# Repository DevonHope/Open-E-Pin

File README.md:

# Open E-Pin

An open-source, battery-powered e-ink pin you can wear on a jacket or bag. It has a round
1.69" colour e-paper display, Bluetooth Low Energy and a small rechargeable battery. You pick
a photo in the Android app, place it in the circle, and the app converts it to the panel's six
colours and sends it to the pin. E-paper keeps the picture with no power at all, so the pin
sleeps until you press its button.

> **Status: v0.2, work in progress.** The board is designed and fully routed, the case is
> modelled and fit-checked against every part, and the firmware and app frameworks build and
> pass their unit tests. v0.2 fixes the findings of a full design audit
> ([hardware/docs/audit](hardware/docs/audit/STATUS.md)). Nothing has been built or run on real
> hardware yet: check the open items in that status table before ordering boards.

## Features

- **Round colour e-paper:** Good Display GDEH0169E02, 1.69", 400 x 400 pixels, six colours
  (Spectra 6). The image stays on screen with the power off.
- **Bluetooth Low Energy:** Nordic nRF52840 in a pre-certified Raytac MDBT50Q-1MV2 module.
- **Tiny sleep current:** the pin sleeps in System OFF (about 0.6 uA estimated, including the
  battery monitor) and only wakes on a button press. The display supply is switched off between refreshes.
- **Small rechargeable battery:** 3.7 V 60 mAh LiPo on a JST-PH connector, so it can be
  unplugged or swapped.
- **Safe charging over USB-C:** TI BQ25101 charger at 30 mA, with a thermistor against the cell
  so it only charges between 0 °C and 60 °C.
- **Protected inputs:** reverse-battery protection, plus a resettable fuse, ESD array and
  overvoltage cutoff on USB.
- **Resumable uploads:** if the Bluetooth link drops mid-transfer, the app picks up where it
  stopped. Each image is checked with a CRC before it's drawn.
- **Printed case** with a clean front, screws from the back and two locking pin-back posts.
- **Fully open:** KiCad schematic and board, case model, firmware and app, plus the scripts
  that generate the hardware files.

## Specifications

| | |
|---|---|
| Display | Good Display GDEH0169E02, 1.69" round, 400 x 400, Spectra 6, 32-pin 0.5 mm FPC |
| MCU / radio | Raytac MDBT50Q-1MV2 (nRF52840, Bluetooth 5, chip antenna) |
| Battery | 3.7 V LiPo, 60 mAh, JST-PH 2.0 mm, cell has its own protection circuit |
| Charging | USB-C, 30 mA, temperature-qualified (BQ25101) |
| Power | 3.0 V LDO (TPS7A0230), switched display rail (TPS22916C) |
| Controls | One side-press button, charge LED |
| Board | 56 mm round with a flat for the display ribbon, 4 layers, all parts on the back |
| Case | 3D-printed bezel and back cover, 60.4 mm across, 10.9 mm thick |
| Firmware | Zephyr / nRF Connect SDK, flashed over SWD test pads |
| App | Android 8.0 (API 26) or newer, Kotlin and Jetpack Compose |

## How it works

```mermaid
flowchart LR
    APP["Android app<br/>crop, dither, pack"] -. "Bluetooth LE" .-> MCU
    USB["USB-C"] --> CHG["Fuse, ESD,<br/>30 mA charger"] --> SYS(("Battery rail"))
    BAT["60 mAh LiPo"] --> RP["Reverse-battery<br/>protection"] --> SYS
    SYS --> LDO["3.0 V LDO"] --> MCU["nRF52840 module"]
    LDO --> SW["Display load switch"] --> EPD["1.69in round e-paper"]
    MCU -- "SPI" --> EPD
    BTN["Side button"] --> MCU
```

1. Press the button. The pin wakes and advertises as `Open E-Pin` for 60 seconds.
2. In the app, pick a photo, drag and pinch it into the circle, and adjust it. The app dithers
   it to the six ink colours and packs it two pixels per byte.
3. The app connects and uploads the image. The pin checks it, switches the display on, draws
   it, switches the display off again and goes back to sleep.

The Bluetooth protocol shared by the app and firmware is in
[`docs/ble-protocol.md`](docs/ble-protocol.md).

## Hardware

The board is a 56 mm round, 4-layer PCB with every part on the back and the display on the
front. The schematic and board are generated from one Python file,
[`hardware/scripts/design.py`](hardware/scripts/design.py), which lists every part and
connection, and the board is autorouted by a script. See the
[hardware README](hardware/README.md) for the block diagram, pin map, safety notes,
regeneration and routing steps, and the open items to check before ordering boards. The parts
list is in [`hardware/bom/open-e-pin-bom.csv`](hardware/bom/open-e-pin-bom.csv), and there is
a [PDF of the schematic](hardware/docs/schematic.pdf) if you don't have KiCad.

## Case

| Exploded view | Back |
|---|---|
|  |  |

A two-part printed case: a **bezel** with the display window, and a **back cover**. Two M2
countersunk thread-forming screws go in from the back into bosses in the bezel, so the front
is just the ring and the display, and two snap hooks hold the top. Two locking tie tack posts
stop the pin from spinning on a bag. They are fitted from inside the back cover, so their heads
can't pull through, and a printed retainer bar holds them in place. A small printed plunger
works the side button.

The [SolidCraft](hardware/case/solidcraft/) design is the master for the case; the printable
STEP and STL files in [`hardware/case/out/`](hardware/case/out/) are exported from it. The
[case README](hardware/case/README.md) has the fastener list, fit-check measurements,
assembly steps and the assumptions to check on real parts.

## Firmware

Zephyr-based firmware for the nRF52840 in [`firmware/`](firmware/). It sleeps in System OFF,
wakes on the button, advertises, receives an image over a custom GATT service, checks its
CRC-32 and draws it on the panel. It also reports battery level through the standard Battery
Service. It builds for the pin board (`open_e_pin/nrf52840`) and for an nRF52840 DK for bench
work, and the transfer logic has unit tests that run on a PC.

The panel driver follows Good Display's sample code for this panel but hasn't been run on
a real panel yet. See the [firmware README](firmware/README.md) for building, flashing, logs over
RTT, and the checklist before powering a real panel.

## Android app

A Kotlin app in [`app/`](app/) that finds the pin, lets you pick an image with the system photo
picker and place it in the round frame, then adjusts, dithers and uploads it. All the image
and protocol logic lives in a plain-Kotlin `core` module with unit tests, and the `android`
module holds the Jetpack Compose UI and BLE code. The UI hasn't been run on a phone yet. See
the [app README](app/README.md) for the image pipeline, building and permissions.

## Repository layout

| Path | What it is |
|---|---|
| [`hardware/`](hardware/) | Main board: KiCad 7 project, generator and routing scripts, BOM, docs |
| [`hardware/case/`](hardware/case/) | Printed case: SolidCraft master, STEP/STL exports, fit check |
| [`firmware/`](firmware/) | nRF52840 firmware (Zephyr / nRF Connect SDK) |
| [`app/`](app/) | Android companion app (Kotlin, Jetpack Compose) |
| [`docs/ble-protocol.md`](docs/ble-protocol.md) | Bluetooth protocol between the app and the pin |
| [`GDEH0169E02.pdf`](GDEH0169E02.pdf) | Display specification from Good Display, kept for reference |

## Roadmap

- [x] Schematic and part selection
- [x] Board placement and routing
- [x] Printed case, fit-checked against the board, battery and display
- [x] Firmware framework: sleep and wake, BLE image transfer with resume, battery reporting
- [x] App framework: image pipeline, dithering, resumable uploader
- [ ] Check the [open items](hardware/README.md) on real parts (display ribbon fold, battery
      thickness, footprints) and order the first boards
- [ ] Port the real panel init sequence and test on a panel
- [ ] Run the app on a phone against the firmware
- [ ] Print and assemble a case
- [ ] Bonding so only a paired phone can send images, and over-the-air firmware updates

## Contributing

Issues and pull requests are welcome, especially reviews of the schematic and case before the
first boards are ordered. A few conventions keep things in sync:

- **Board:** edit `hardware/scripts/design.py` and regenerate rather than editing the KiCad
  files by hand.
- **Case:** edit the SolidCraft design and re-export to `hardware/case/out/`.
- **Protocol:** change [`docs/ble-protocol.md`](docs/ble-protocol.md) first, then the firmware
  and app together.

## License

GPL-3.0. See [LICENSE](LICENSE).

The display specification (`GDEH0169E02.pdf`) is © Good Display and is included only for
reference. It is not covered by this project's license.

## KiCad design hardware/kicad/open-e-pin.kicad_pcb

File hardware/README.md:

# Open E-Pin hardware

KiCad 7 project for the main board. The schematic and board are **generated** from
[`scripts/design.py`](scripts/design.py), which lists every part and every connection.
Change the design there, then regenerate, so the schematic and board never drift apart.

## Files

| Path | What it is |
|---|---|
| `kicad/open-e-pin.kicad_sch` | Schematic (one sheet, every pin labelled with its net) |
| `kicad/open-e-pin.kicad_pcb` | Board: 56 mm round with a flat for the display ribbon, 2 case-screw holes (4.6 mm, unplated, for the bezel's screw bosses), 2 notches for the case's snap hooks, 3 fiducials, 4 layers (0.8 mm), placed and routed |
| `kicad/open-e-pin.kicad_pro` | Project, including the net classes and board rules the board is routed to (written by `route.py prep`), so KiCad's DRC checks the real rules |
| `kicad/open-e-pin.kicad_sym` | Custom symbols (BQ25101, TPS7A0230, TPS22916C, GDEH0169E02 FPC) |
| `kicad/OpenEPin.pretty` | Custom footprints for TI's YFP packages (BQ25101, TPS22916C), written by `scripts/gen_footprints.py` |
| `case/` | Printed case, fit check and fastener list, see [case/README.md](case/README.md) |
| `bom/open-e-pin-bom.csv` | Bill of materials: manufacturer part numbers for every part, plus the battery, display, case parts, fasteners, pin hardware and consumables |
| `fab/` | Fabrication and assembly outputs (Gerber X2, drill, IPC-D-356 netlist, pick-and-place, fab notes), written by `scripts/gen_fab.sh` |
| `docs/audit/` | v0.1 design and manufacturing audit, and the status of each finding |
| `docs/schematic.pdf` | Schematic as a PDF |
| `docs/placement-back.png`, `docs/placement.csv` | Part placement view and coordinates |
| `docs/routing.png` | Back and front copper |
| `scripts/` | `design.py` (parts and nets), `gen_footprints.py`, `gen_schematic.py`, `gen_board.py`, `route.py`, `gen_bom.py`, `export_envelope.py` (part sizes for the case) |

## Regenerating

Needs KiCad 7 and its Python module (`pcbnew`). On Linux the system `python3` has it; on
Windows use the Python that ships with KiCad (`C:\Program Files\KiCad\7.0\bin\python.exe`)
and set `KICAD7_SYMBOL_DIR` and `KICAD7_FOOTPRINT_DIR` to KiCad's `share\kicad\symbols` and
`share\kicad\footprints` folders.

```
cd hardware/scripts
python3 design.py          # checks parts and nets
python3 gen_footprints.py  # writes kicad/OpenEPin.pretty
python3 gen_schematic.py   # writes kicad/open-e-pin.kicad_sch and the symbol library
python3 gen_board.py       # writes kicad/open-e-pin.kicad_pcb (overwrites placement!)
python3 gen_bom.py         # writes bom/open-e-pin-bom.csv
```

After routing (below), `./gen_fab.sh` writes the fabrication files to `fab/`.

### Routing

`gen_board.py` writes an unrouted board, so routing is redone after it. Needs Java 17 or later
and [Freerouting 1.9.0](https://github.com/freerouting/freerouting/releases/tag/v1.9.0)
(2.x ignores its pass limit when run from the command line and never saves).

```
python3 route.py prep      # rules, net classes, planes, GND/3V0 via fan-out; writes build/open-e-pin.dsn
java -jar freerouting-1.9.0.jar -de ../build/open-e-pin.dsn -do ../build/open-e-pin.ses -mp 100
python3 route.py import ../build/open-e-pin.ses
```

On a Linux machine with no screen, put `xvfb-run -a` in front of the `java` command.
`import` loads the autorouted tracks, fans out any GND/3V0 pad the autorouter boxed in
(ripping up the signal tracks round it if it has to),
rips up and re-routes any net that is still open or breaks clearance (a small maze router in
`route.py`), then adds GND pours on both outer layers and stitches them to the GND plane.

Stackup: B.Cu parts and signals, In1.Cu solid GND, In2.Cu 3V0 plane, F.Cu signals and GND
pour under the display. Rules (net classes in `kicad/open-e-pin.kicad_pro`): 0.15 mm tracks and
clearance, 0.2 mm for power (narrow enough to leave the 0.4 mm-pitch TI WCSP balls, and
`EPD_VDD` is in this class), 0.3 mm for the display booster, and 0.2 mm tracks with 0.2 mm
spacing for every panel rail (`PanelHV`: VGH, VGL, VSH1-3, VSL1-3, VCOM, VREFR, VREFL, VDDL).
Vias are 0.5/0.25 mm; no via is placed in or touching an SMD land (the DSN sets
`via_at_smd off`, and `route.py` removes and re-routes any it finds). The antenna keep-out is
clear of copper on every layer.

Once you start editing the routing by hand in KiCad, stop running `gen_board.py` and
`route.py` on it, and use **Tools > Update PCB from Schematic** instead.

## Block diagram

```mermaid
flowchart TD
    USB["USB-C J1, CC 5.1k pull-downs"] --> F1["PTC fuse F1 0.1 A"]
    F1 --> ESD["USBLC6-2 ESD U5"]
    ESD --> CHG["BQ25101 charger U2, 30 mA"]
    ESD -- "D+ / D-, VBUS sense" --> MCU
    NTC["10k NTC at the cell edge"] -- TS --> CHG
    CHG -- "charge status" --> LED["Charge LED"]
    CHG -- "charge status" --> MCU
    CHG --> VSYS(("VBAT_SYS"))
    BAT["LiPo 60 mAh, JST-PH, own protection"] --> RP["Reverse-battery FETs Q1 + Q2"]
    RP --> VSYS
    VSYS -- "470k: wakes a cut-off cell" --> RP
    VSYS -- "10M/10M divider" --> MCU
    VSYS --> LDO["TPS7A0230 LDO U3, 3.0 V"]
    LDO --> MCU["nRF52840 module U1"]
    LDO --> LSW["TPS22916C load switch U4"]
    MCU -- "EPD_PWR_EN" --> LSW
    LSW --> EPD["1.69in round e-paper GDEH0169E02"]
    BOOST["Booster L1, Q3, D1-D3, R8, R15"] --> EPD
    MCU -- "SPI + CS / DC / RST / BUSY" --> EPD
    BTN["Side button SW1, 1k series"] --> MCU
    SWD["SWD test pads"] --> MCU
```

## Safety features

- Charge current set to 30 mA (0.5C for a 60 mAh cell) by R1 (4.53k, 27.6 to 32 mA over the
  charger's tolerance). The CM Batteries 55 mAh option allows 28 mA at most: fit R1 = 5.62k (about 24 mA).
- The charger (JEITA profile) pauses below 0 °C, charges to 4.06 V instead of 4.20 V between
  45 and 60 °C, and stops above 60 °C. The NTC (RT1) sits at the edge of the cell with a thermal
  pad to the pouch. **Check the cell's datasheet:** if it does not allow charging above 45 °C
  (most small pouch cells give 0 to 45 °C), the cell is outside its rating in that band; see the
  open items.
- The BQ25101 itself withstands 30 V and stops charging above about 6.7 V, but the same VBUS
  net also feeds the nRF52840's VBUS pin (5.8 V absolute maximum) and the USB ESD array (U5),
  so the board as a whole is rated for USB voltages (5.5 V max), not 30 V. A 0.1 A resettable
  fuse and the ESD array protect the USB port.
- Reverse-battery protection (Q1, Q2) blocks a backwards cell, including when USB is plugged in.
- R16 (470k, VBAT_SYS to Q2's gate) turns Q1 on from the charger, so a cell whose own
  protection has cut off after a deep discharge still sees the charger and can recover. With a
  reversed cell Q2's gate stays at least 2.3 V below its source, so the protection still holds.
- The cell's own protection circuit covers over-discharge, overcharge and short circuit; the
  board has no separate fuse on the battery, so use a cell with a protection circuit and
  IEC 62133-2 / UN 38.3 reports only.
- Standby drain from the board is about 1.1 µA besides the nRF52840 (R2/R3 divider 0.21 µA,
  R4 0.42 µA, LDO 25 nA, charger 75 nA, load switch leakage), about 3 µA in all.

## MCU pin map

| Signal | nRF52840 | Module pin |
|---|---|---|
| EPD_SCK / EPD_MOSI | P0.22 / P0.24 | 46 / 48 |
| EPD_CS / EPD_DC | P0.20 / P0.17 | 44 / 41 |
| EPD_RST / EPD_BUSY | P0.15 / P0.13 | 39 / 37 |
| EPD_PWR_EN | P1.00 | 47 |
| VBAT_SENSE (AIN5) | P0.29 | 10 |
| CHG_SENSE | P0.31 | 12 |
| BUTTON (active low, through R17 1k) | P1.06 | 57 |
| USB D+ / D- | USB | 35 / 34 |
| SWDIO / SWDCLK / RESET | SWD, P0.18 | 51 / 53 / 40 |

## Open items before ordering boards

The v0.1 audit and the status of every finding are in [docs/audit/](docs/audit/).

1. **Display FPC orientation (fixed in v0.2, confirm on a panel):** v0.1 wired J3 mirror-image.
   The panel's pin 1 is on the left in its front view (tail down), the tail folds 180 degrees
   round the board's flat edge into a bottom-contact Hirose FH12-32S-0.5SH(55) on the back, and
   the fold keeps each finger's x position, so panel pin n lands on J3 pad 33 - n
   (`design.fpc()`; `gen_board.py` refuses to write a mirrored board). Before ordering, fold a real
   panel's tail over a printout of the board and check that pin 1 (VREFR) meets the pad marked
   EPD_VREFR, at the left end seen from the front.
2. **Display wiring:** all 32 pins follow figures 7-1 and 7-2 of the GDEH0169E02
   specification (IST7601 / JD7601 controller). Panel VDD (pin 15) runs from the switched 3.0 V
   rail. The rail capacitors (C11 to C24) are 1 uF 50 V X7R 0603 (the spec asks for 0603 25 V;
   50 V keeps their capacitance at the 15 to 20 V rails). Pins 7 and 25 to 32 are left open as
   the reference shows. BS0 is pulled low for 4-wire SPI. The spec still lists refresh current as
   TBD; measure it on the first build.
3. **TI WCSP parts:** BQ25101 (YFP0006) and TPS22916C (YFP0004) are 0.4 mm-pitch WCSP with
   NSMD lands (0.23 mm copper, 0.30 mm mask, 0.25 mm paste). They need an assembler that does
   0.4 mm pitch (JLCPCB Standard PCBA, not Economic) and a 0.08 mm stencil; see `fab/README.md`.
4. **Battery:** get the cell's datasheet, UN 38.3 and IEC 62133-2 reports, lead polarity
   (J2 pin 1 = + = red) and measured thickness before ordering (the case allows 5.0 mm). If its
   charge temperature limit is 45 °C, either accept the JEITA 4.06 V band up to 60 °C or move the
   hot cut-off down with a TS resistor network.
5. **Booster:** the loop is now placed tight (C24 and C10 at L1, R15 at Q3); L1 (NRH3010, about
   0.25 A saturation) is the part the panel reference names, but the IST7601's current limit is
   not published, so check L1's current on the first build with a current probe.
6. **Antenna:** the display glass reaches about 1 mm into the module's antenna keep-out (no
   copper there on any layer). Do a range test with the panel and case fitted.
7. **DRC:** with the project's rules, DRC reports only the 4 hole-clearance items inside KiCad's
   own GCT USB4105 footprint (its plastic pegs sit 0.19 mm from two pads, as in GCT's
   recommended layout) and cosmetic silkscreen items.

## Display references

- [GDEH0169E02 product page](https://www.good-display.com/product/874.html): 1.69" round, 400 x 400, Spectra 6, 43 x 43 mm active area, 52.8 x 49.6 x 0.85 mm outline, 0 to 50 °C
- [GDEH0169E02 specification download](https://www.good-display.com/companyfile/2145.html)
- [ESP32 sample code download](https://www.good-display.com/companyfile/2147.html), for porting the driver
- [Buy: GDEH0169E02 at buy-lcd](https://buy-lcd.com/products/gdeh0169e02?VariantsId=11312)

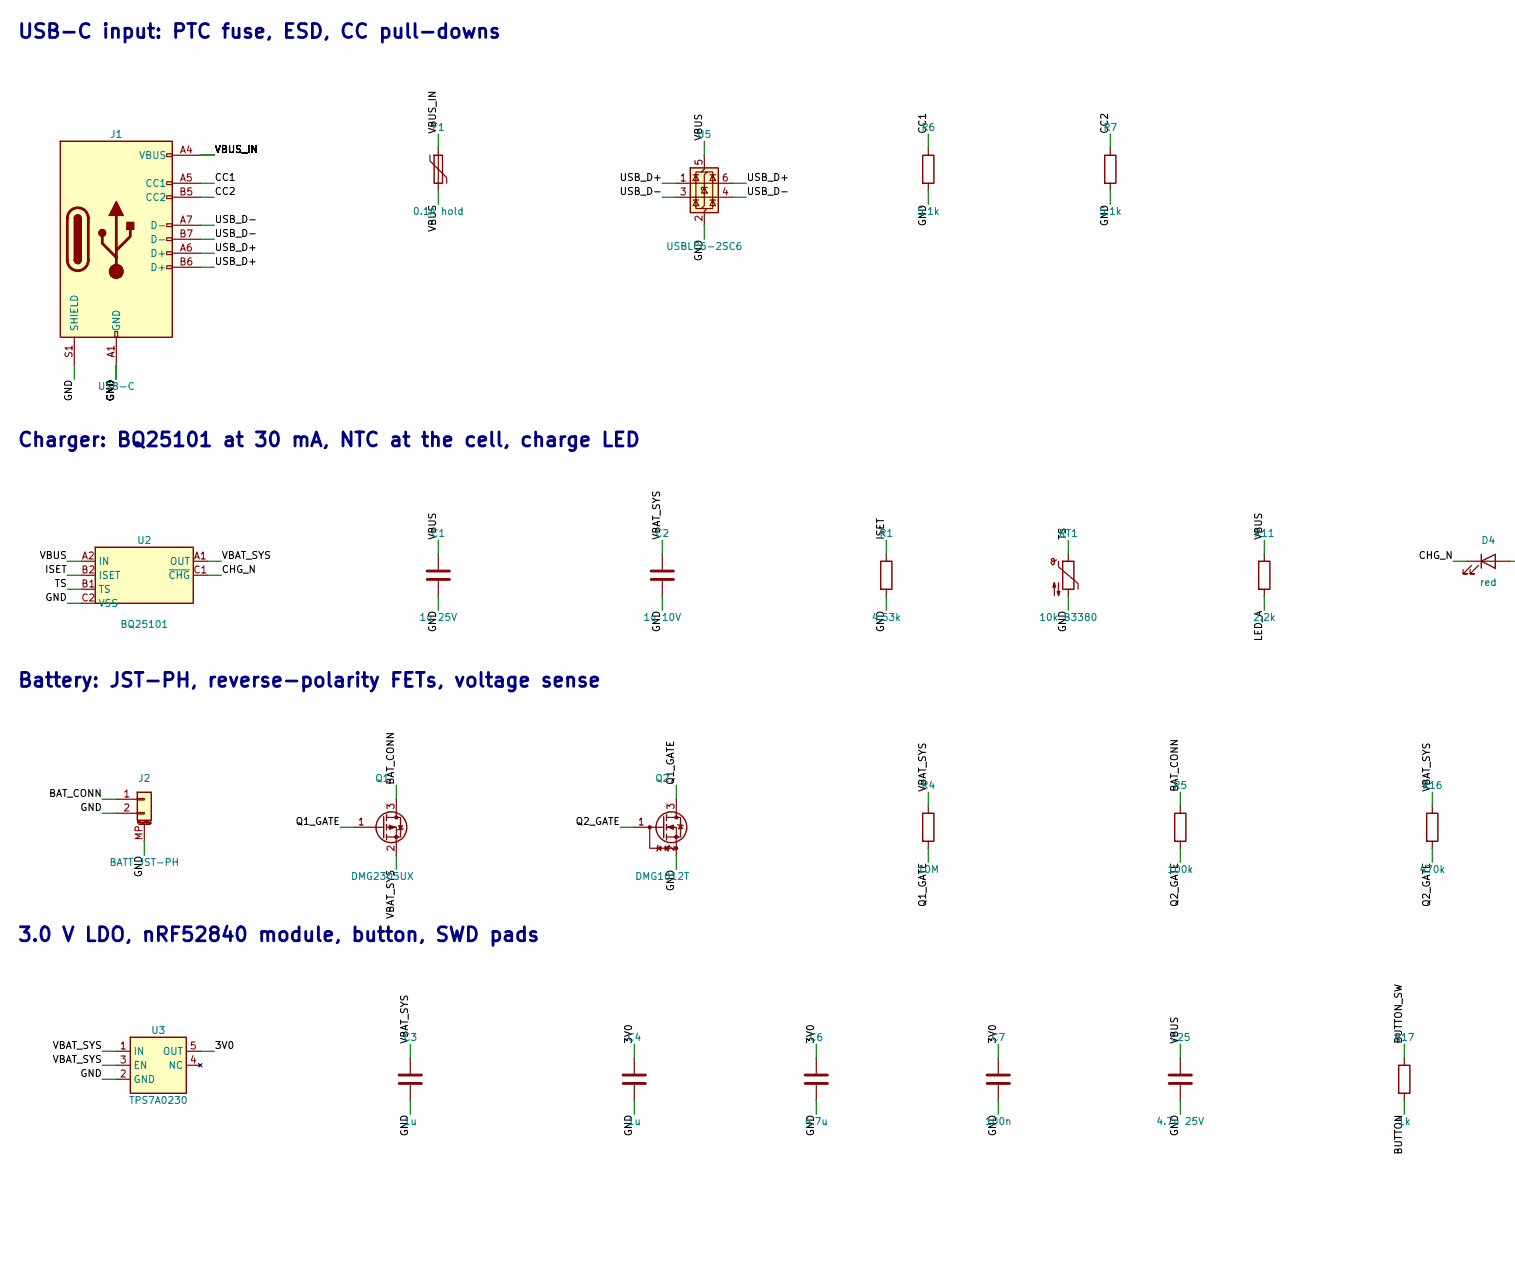
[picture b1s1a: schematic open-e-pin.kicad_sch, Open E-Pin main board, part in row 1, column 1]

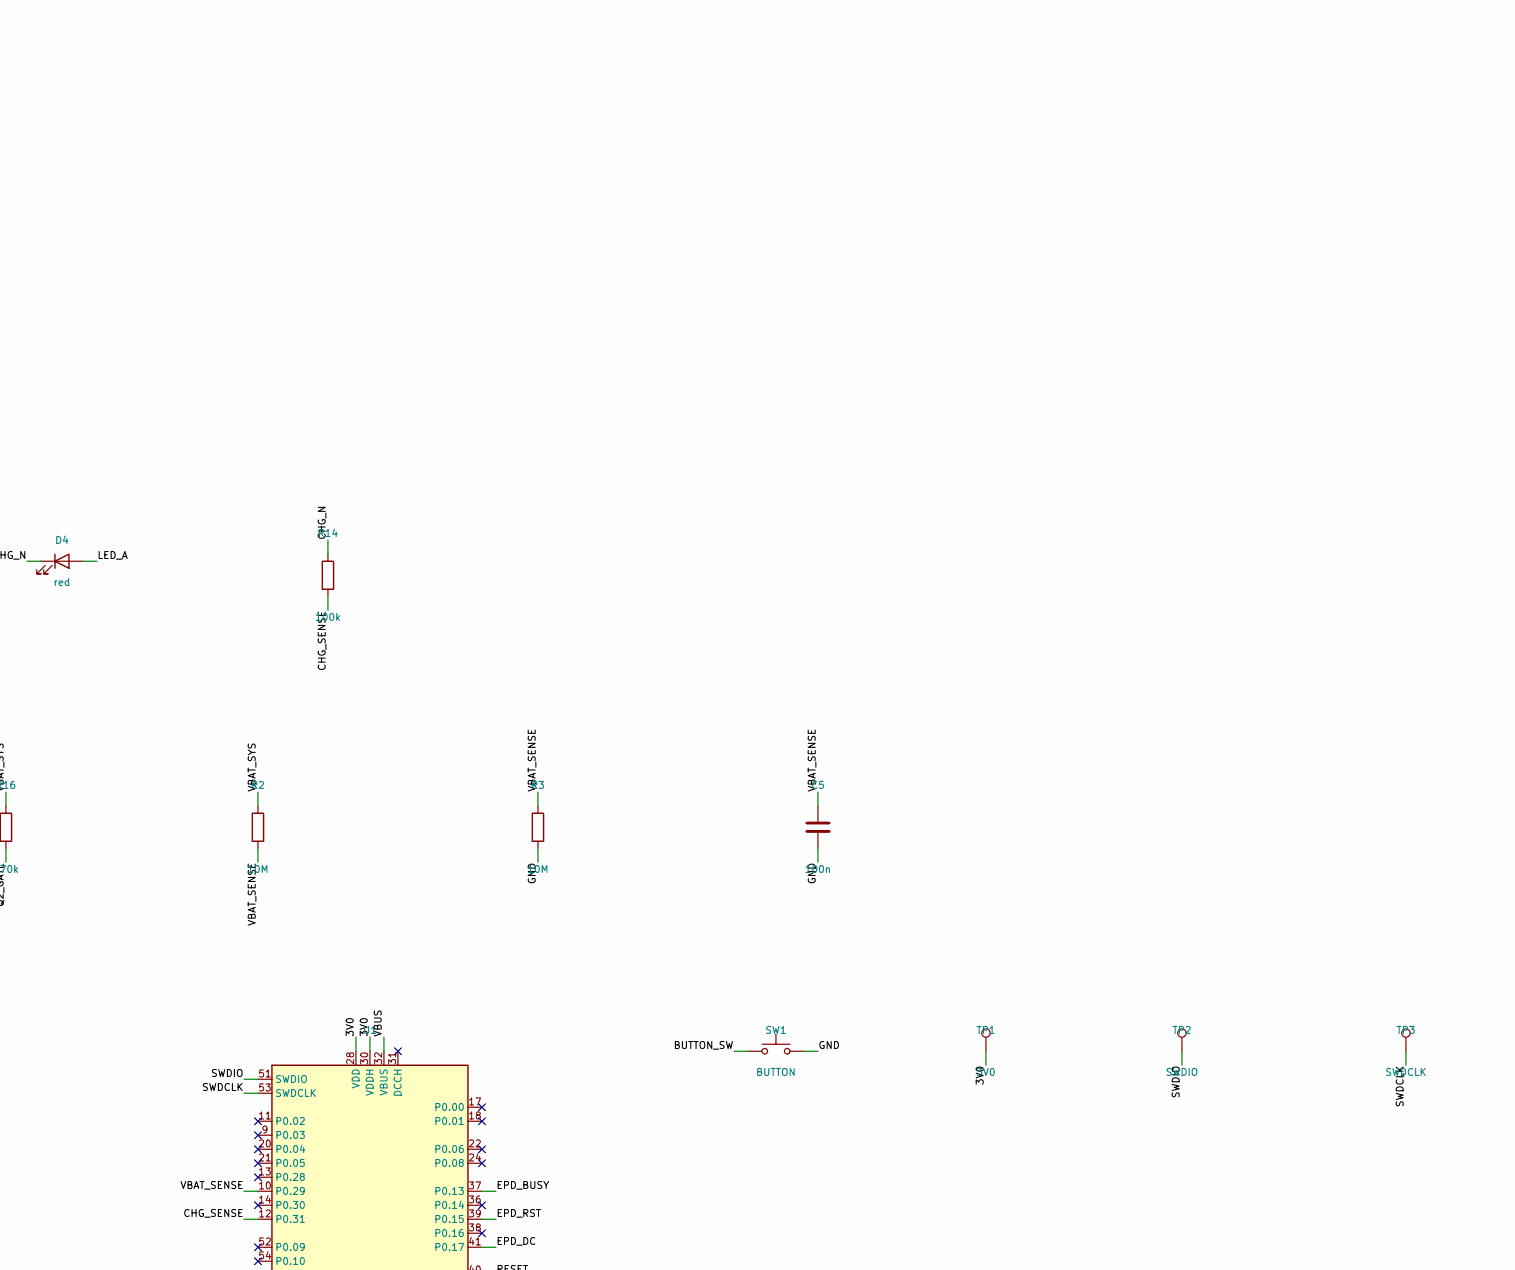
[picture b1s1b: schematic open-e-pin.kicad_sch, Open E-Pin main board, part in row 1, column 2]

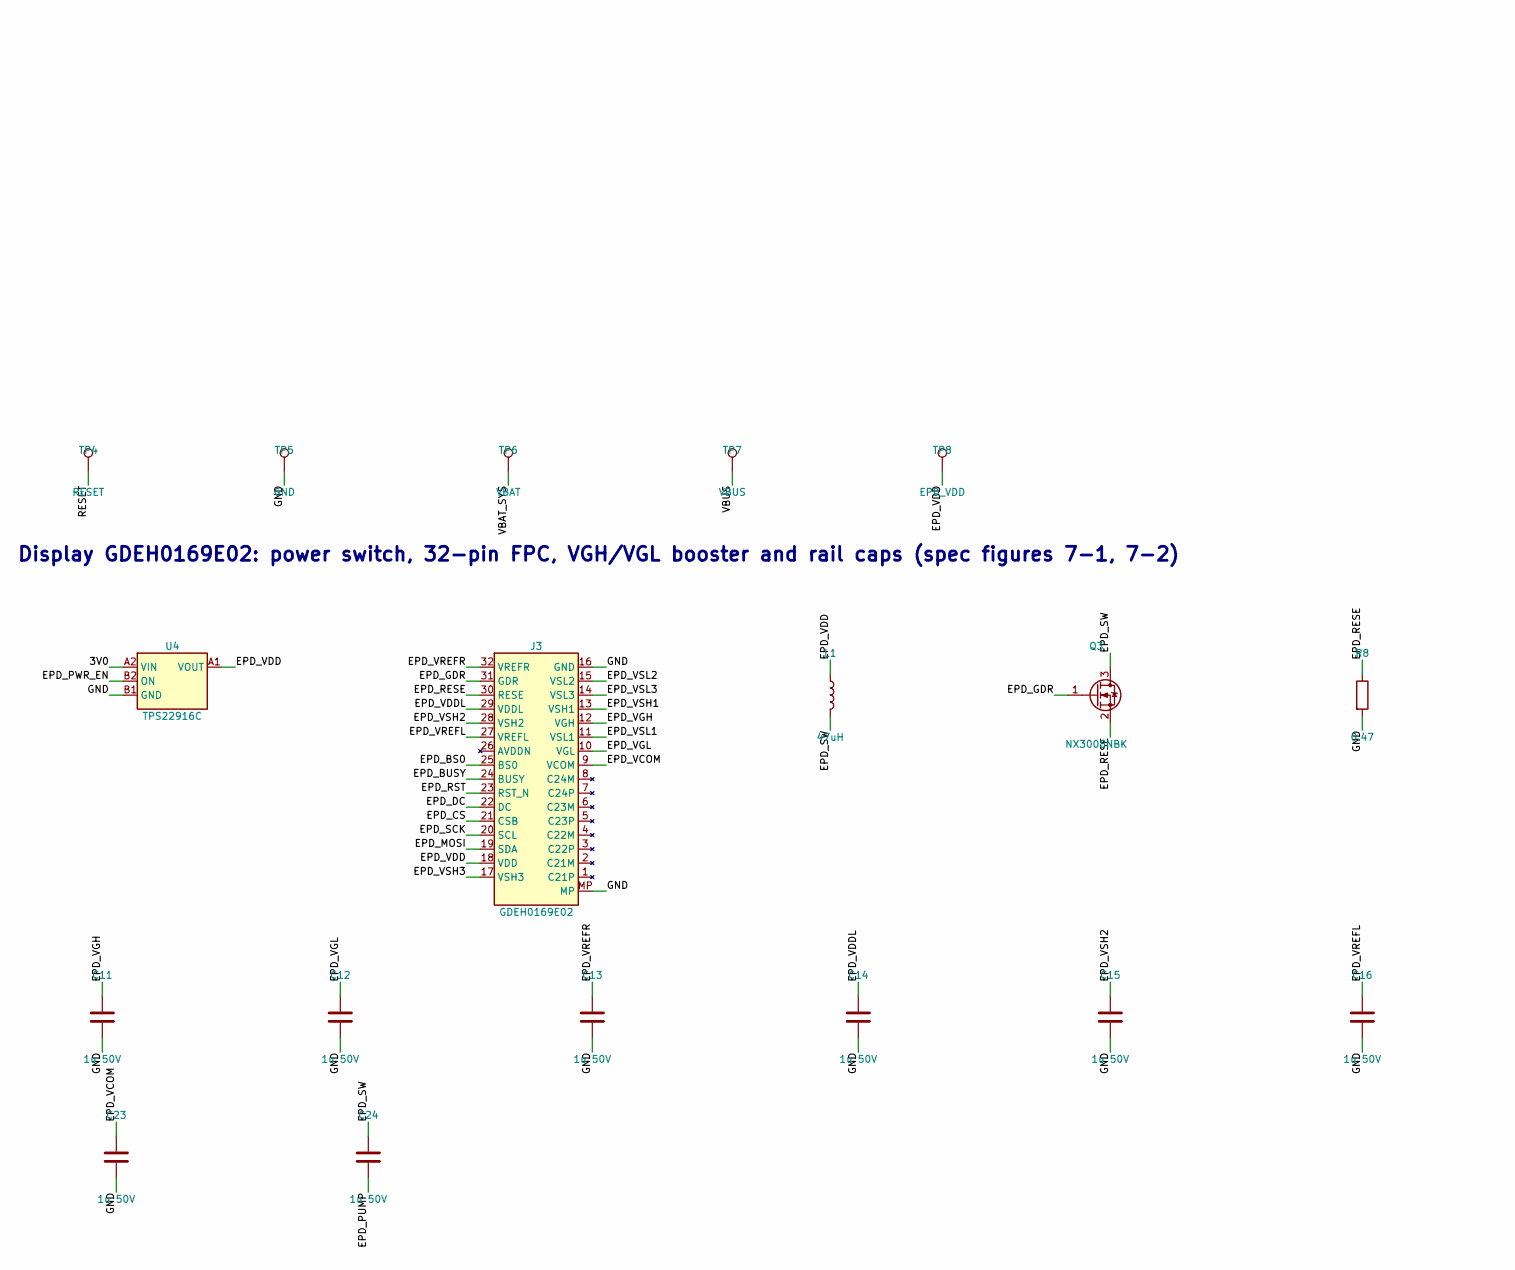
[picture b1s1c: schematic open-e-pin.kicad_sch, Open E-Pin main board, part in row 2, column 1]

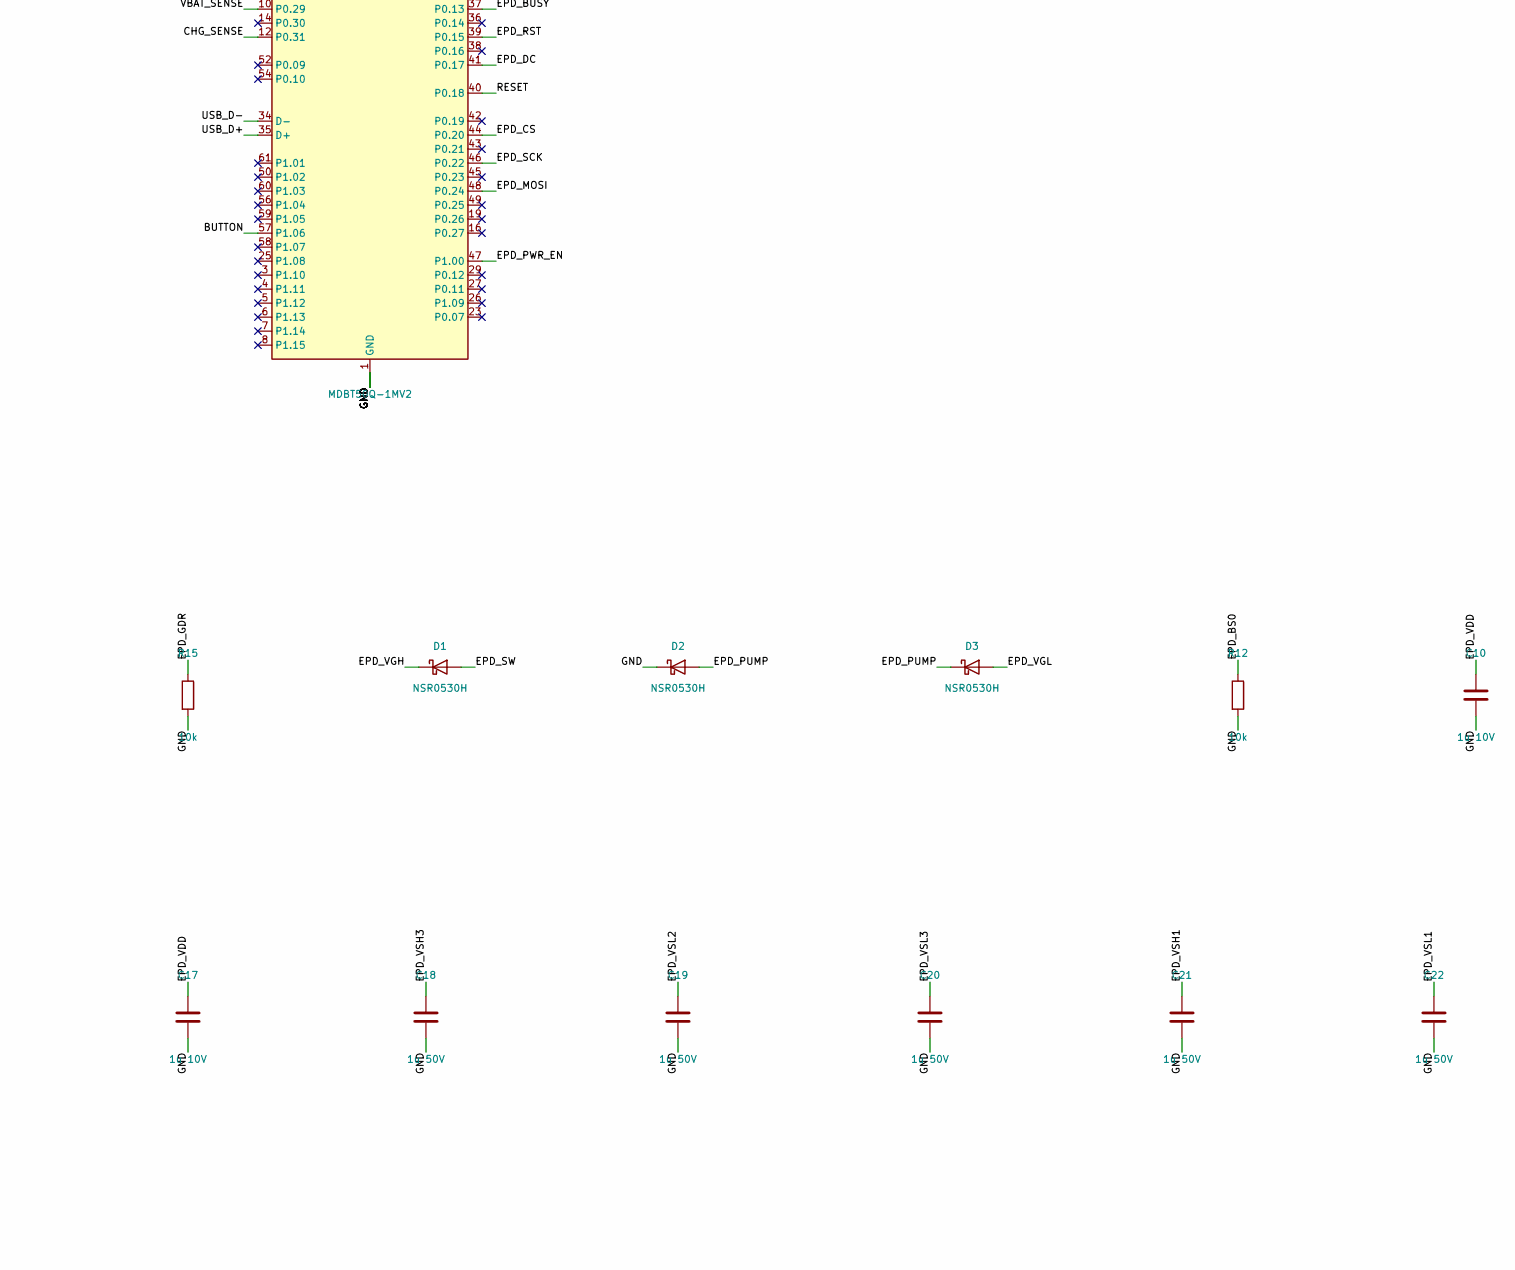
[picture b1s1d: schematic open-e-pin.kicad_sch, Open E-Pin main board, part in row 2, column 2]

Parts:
C1: 1u 25V; C_0402_1005Metric
C2, C10, C17: 1u 10V; C_0402_1005Metric
C3, C4: 1u; C_0402_1005Metric
C5, C7: 100n; C_0402_1005Metric
C6: 4.7u; C_0402_1005Metric
C11, C12, C13, C14, C15, C16, C18, C19, C20, C21, C22, C23, C24: 1u 50V; C_0603_1608Metric
C25: 4.7u 25V; C_0603_1608Metric
D1, D2, D3: NSR0530H; D_SOD-323
D4: red; LED_0402_1005Metric
F1: 0.1A hold; Fuse_0603_1608Metric
J1: USB-C; USB_C_Receptacle_GCT_USB4105-xx-A_16P_TopMnt_Horizontal
J2: BATT JST-PH; JST_PH_S2B-PH-SM4-TB_1x02-1MP_P2.00mm_Horizontal
J3: GDEH0169E02; Hirose_FH12-32S-0.5SH_1x32-1MP_P0.50mm_Horizontal
L1: 47uH; L_Taiyo-Yuden_NR-30xx
Q1: DMG2305UX; SOT-23
Q2: DMG1012T; SOT-523
Q3: NX3008NBK; SOT-23
R1: 4.53k; R_0402_1005Metric
R2, R3, R4: 10M; R_0402_1005Metric
R5, R14: 100k; R_0402_1005Metric
R6, R7: 5.1k; R_0402_1005Metric
R8: 0.47; R_0603_1608Metric
R11: 2.2k; R_0402_1005Metric
R12, R15: 10k; R_0402_1005Metric
R16: 470k; R_0402_1005Metric
R17: 1k; R_0402_1005Metric
RT1: 10k B3380; R_0402_1005Metric
SW1: BUTTON; SW_SPST_EVQP7A
TP1: 3V0; TestPoint_Pad_1.0x1.0mm
TP2: SWDIO; TestPoint_Pad_1.0x1.0mm
TP3: SWDCLK; TestPoint_Pad_1.0x1.0mm
TP4: RESET; TestPoint_Pad_1.0x1.0mm
TP5: GND; TestPoint_Pad_1.0x1.0mm
TP6: VBAT; TestPoint_Pad_1.0x1.0mm
TP7: VBUS; TestPoint_Pad_1.0x1.0mm
TP8: EPD_VDD; TestPoint_Pad_1.0x1.0mm
U1: MDBT50Q-1MV2; Raytac_MDBT50Q
U2: BQ25101; Texas_YFP0006_DSBGA-6_0.9x1.6mm_P0.4mm
U3: TPS7A0230; SOT-23-5
U4: TPS22916C; Texas_YFP0004_DSBGA-4_0.78x0.78mm_P0.4mm
U5: USBLC6-2SC6; SOT-23-6

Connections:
3V0: C4.1, C6.1, C7.1, TP1.1, U1.28 (VDD), U1.30 (VDDH), U3.5 (OUT), U4.A2 (VIN)
BAT_CONN: J2.1, Q1.3 (D), R5.1
BUTTON: R17.2, U1.57 (P1.06)
BUTTON_SW: R17.1, SW1.1
CC1: J1.A5 (CC1), R6.1
CC2: J1.B5 (CC2), R7.1
CHG_N: D4.1 (K), R14.1, U2.C1 (~CHG)
CHG_SENSE: R14.2, U1.12 (P0.31)
EPD_BS0: J3.25 (BS0), R12.1
EPD_BUSY: J3.24 (BUSY), U1.37 (P0.13)
EPD_CS: J3.21 (CSB), U1.44 (P0.20)
EPD_DC: J3.22 (DC), U1.41 (P0.17)
EPD_GDR: J3.31 (GDR), Q3.1 (G), R15.1
EPD_MOSI: J3.19 (SDA), U1.48 (P0.24)
EPD_PUMP: C24.2, D2.2 (A), D3.1 (K)
EPD_PWR_EN: U1.47 (P1.00), U4.B2 (ON)
EPD_RESE: J3.30 (RESE), Q3.2 (S), R8.1
EPD_RST: J3.23 (RST_N), U1.39 (P0.15)
EPD_SCK: J3.20 (SCL), U1.46 (P0.22)
EPD_SW: C24.1, D1.2 (A), L1.2, Q3.3 (D)
EPD_VCOM: C23.1, J3.9 (VCOM)
EPD_VDD: C10.1, C17.1, J3.18 (VDD), L1.1, TP8.1, U4.A1 (VOUT)
EPD_VDDL: C14.1, J3.29 (VDDL)
EPD_VGH: C11.1, D1.1 (K), J3.12 (VGH)
EPD_VGL: C12.1, D3.2 (A), J3.10 (VGL)
EPD_VREFL: C16.1, J3.27 (VREFL)
EPD_VREFR: C13.1, J3.32 (VREFR)
EPD_VSH1: C21.1, J3.13 (VSH1)
EPD_VSH2: C15.1, J3.28 (VSH2)
EPD_VSH3: C18.1, J3.17 (VSH3)
EPD_VSL1: C22.1, J3.11 (VSL1)
EPD_VSL2: C19.1, J3.15 (VSL2)
EPD_VSL3: C20.1, J3.14 (VSL3)
GND: C1.2, C2.2, C3.2, C4.2, C5.2, C6.2, C7.2, C10.2, C11.2, C12.2, C13.2, C14.2, C15.2, C16.2, C17.2, C18.2, C19.2, C20.2, C21.2, C22.2, C23.2, C25.2, D2.1 (K), J1.A1 (GND), J1.A12 (GND), J1.B1 (GND), J1.B12 (GND), J1.S1 (SHIELD), J2.2, J2.MP (MountPin), J3.16 (GND), J3.MP, Q2.2 (S), R1.2, R3.2, R6.2, R7.2, R8.2, R12.2, R15.2, RT1.2, SW1.2, TP5.1, U1.1 (GND), U1.2 (GND), U1.15 (GND), U1.33 (GND), U1.55 (GND), U2.C2 (VSS), U3.2 (GND), U4.B1 (GND), U5.2 (GND)
ISET: R1.1, U2.B2 (ISET)
LED_A: D4.2 (A), R11.2
Q1_GATE: Q1.1 (G), Q2.3 (D), R4.2
Q2_GATE: Q2.1 (G), R5.2, R16.2
RESET: TP4.1, U1.40 (P0.18)
SWDCLK: TP3.1, U1.53 (SWDCLK)
SWDIO: TP2.1, U1.51 (SWDIO)
TS: RT1.1, U2.B1 (TS)
USB_D+: J1.A6 (D+), J1.B6 (D+), U1.35 (D+), U5.1 (I/O1), U5.6 (I/O1)
USB_D-: J1.A7 (D-), J1.B7 (D-), U1.34 (D-), U5.3 (I/O2), U5.4 (I/O2)
VBAT_SENSE: C5.1, R2.2, R3.1, U1.10 (P0.29)
VBAT_SYS: C2.1, C3.1, Q1.2 (S), R2.1, R4.1, R16.1, TP6.1, U2.A1 (OUT), U3.1 (IN), U3.3 (EN)
VBUS: C1.1, C25.1, F1.2, R11.1, TP7.1, U1.32 (VBUS), U2.A2 (IN), U5.5 (VBUS)
VBUS_IN: F1.1, J1.A4 (VBUS), J1.A9 (VBUS), J1.B4 (VBUS), J1.B9 (VBUS)

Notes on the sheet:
USB-C input: PTC fuse, ESD, CC pull-downs
Charger: BQ25101 at 30 mA, NTC at the cell, charge LED
Battery: JST-PH, reverse-polarity FETs, voltage sense
3.0 V LDO, nRF52840 module, button, SWD pads
Display GDEH0169E02: power switch, 32-pin FPC, VGH/VGL booster and rail caps (spec figures 7-1, 7-2)

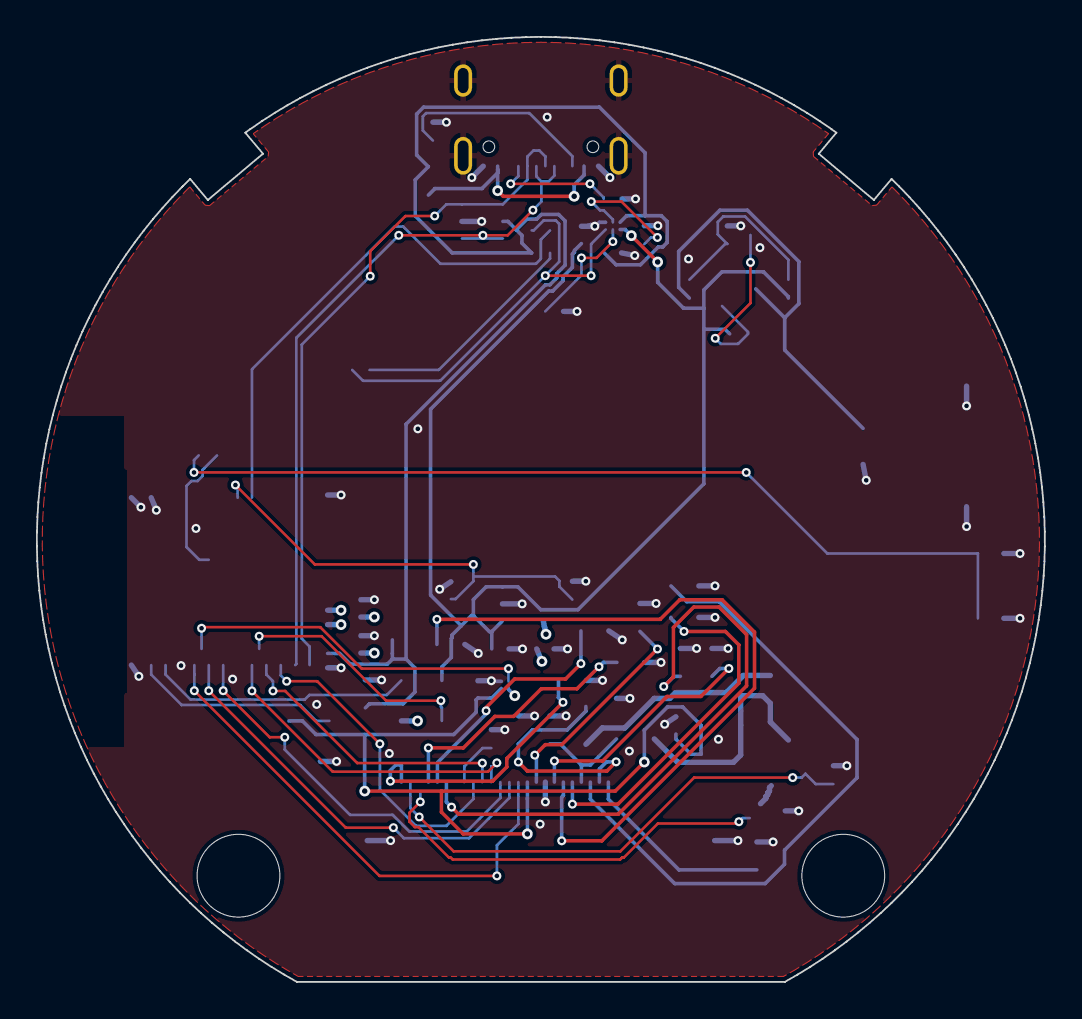
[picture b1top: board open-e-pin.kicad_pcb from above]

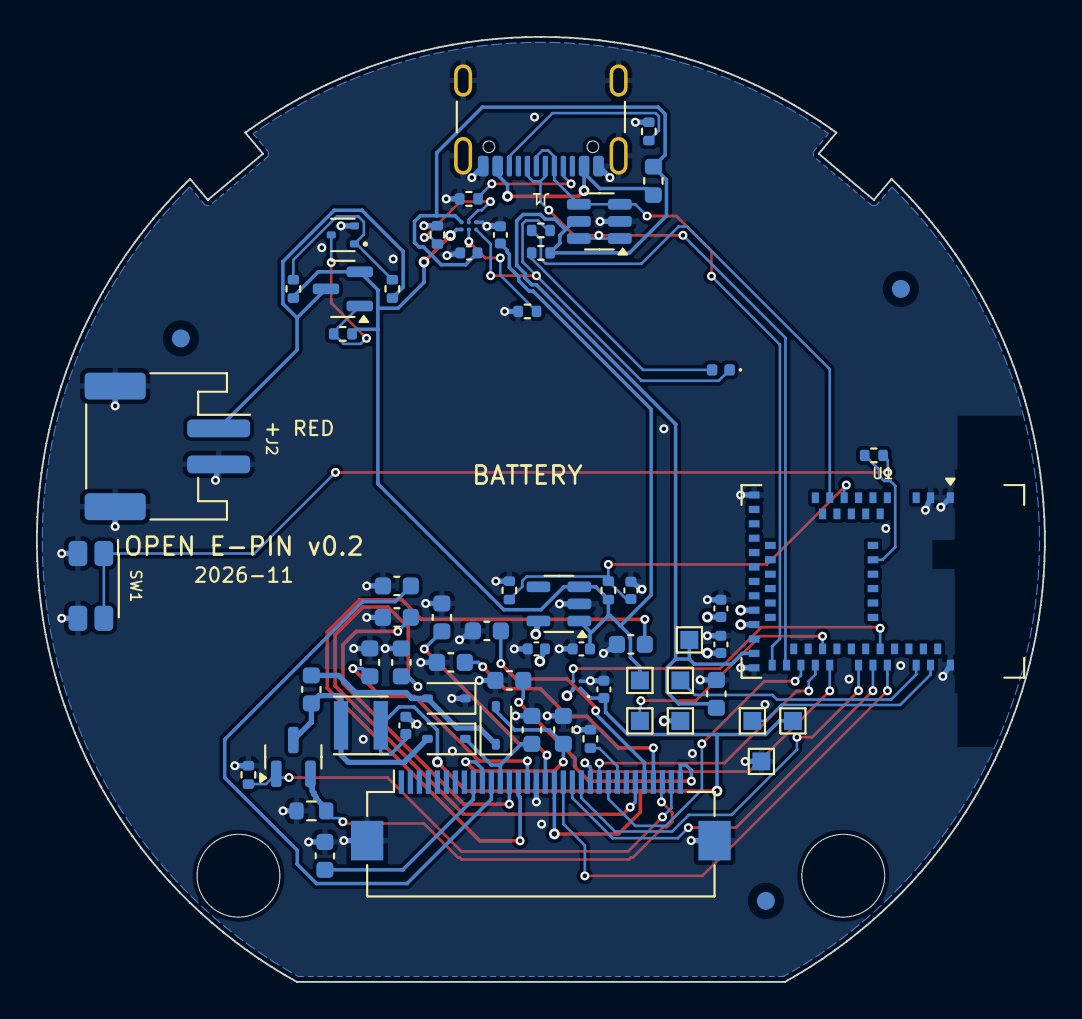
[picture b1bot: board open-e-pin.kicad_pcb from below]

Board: 4 copper layers, 56.0 x 52.5 mm, 69 parts (67 on the bottom side), 48 nets.

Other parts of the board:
FID1, FID2, FID3: Fiducial; Fiducial_1mm_Mask2mm
H1, H2: M2; MountingHole_4.6mm_CaseBoss

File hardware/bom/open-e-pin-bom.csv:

References,Qty,Value,Footprint,Part number / note
C1 C10 C11 C12 C13 C14 C15 C16 C17 C18 C19 C21 C22 C23 C24,15,1u 25V,Capacitor_SMD:C_0402_1005Metric,"C1: X5R; C10: EPD_VDD (VCCI) 1u, X5R; C11: VGH, X5R; C12: VGL, X5R; C13: pin 1 VREFR, X5R; C14: pin 4 VDDL, X5R; C15: pin 5 VSH2, X5R; C16: pin 6 VREFL, X5R; C17: pin 15 VDD, X5R; C18: pin 16 VSH3, X5R; C19: pin 18 VSL2, X5R; C21: pin 20 VSH1, X5R; C22: pin 22 VSL1, X5R; C23: pin 24 VCOM, X5R; C24: charge-pump flying cap, X5R"
C2,1,1u 10V,Capacitor_SMD:C_0402_1005Metric,X5R
C3 C4,2,1u,Capacitor_SMD:C_0402_1005Metric,
C5 C7,2,100n,Capacitor_SMD:C_0402_1005Metric,C5: ADC hold; C7: module VDD
C6,1,4.7u,Capacitor_SMD:C_0402_1005Metric,module VDD bulk
C20,1,1u 35V,Capacitor_SMD:C_0402_1005Metric,"pin 19 VSL3 (35 V per reference), X5R"
D1 D2 D3,3,NSR0530H,Diode_SMD:D_SOD-323,"D1: VGH diode. 30 V, 0.5 A, Vf<=430 mV (MBR0530 class); D2: charge pump to GND. 30 V, 0.5 A, Vf<=430 mV; D3: VGL diode. 30 V, 0.5 A, Vf<=430 mV"
F1,1,0.1A hold,Fuse:Fuse_0603_1608Metric,Bourns MF-PSMF010X-2
J1,1,USB-C,Connector_USB:USB_C_Receptacle_GCT_USB4105-xx-A_16P_TopMnt_Horizontal,GCT USB4105-GF-A
J2,1,BATT JST-PH,Connector_JST:JST_PH_S2B-PH-SM4-TB_1x02-1MP_P2.00mm_Horizontal,JST S2B-PH-SM4-TB. Pin 1 = +
J3,1,GDEH0169E02,Connector_FFC-FPC:Hirose_FH12-32S-0.5SH_1x32-1MP_P0.50mm_Horizontal,Hirose FH12-32S-0.5SH. VERIFY contact side: panel FPC contacts face the board after the fold
L1,1,47uH,Inductor_SMD:L_Taiyo-Yuden_NR-30xx,Taiyo Yuden NRH3010T470MN
LED1,1,red,LED_SMD:LED_0402_1005Metric,charge indicator
Q1,1,DMG2305UX,Package_TO_SOT_SMD:SOT-23,Diodes DMG2305UX-7
Q2,1,DMG1012T,Package_TO_SOT_SMD:SOT-523,Diodes DMG1012T-7
Q3,1,NX3008NBK,Package_TO_SOT_SMD:SOT-23,"Nexperia NX3008NBK or Vishay Si1304BDL (Vds>=30V, Vgs(th) 1.3V max)"
R1,1,4.53k,Resistor_SMD:R_0402_1005Metric,ISET: 135/4530 = 30 mA (use 5.6k for 24 mA cells)
R4 R2 R3,3,10M,Resistor_SMD:R_0402_1005Metric,"R4: Q1 gate pull-up; R2: battery divider top, 1%; R3: battery divider bottom, 1%"
R6 R7,2,5.1k,Resistor_SMD:R_0402_1005Metric,1%
R8,1,0.47,Resistor_SMD:R_0603_1608Metric,"1%, booster current sense"
R11,1,2.2k,Resistor_SMD:R_0402_1005Metric,
R14 R5,2,100k,Resistor_SMD:R_0402_1005Metric,R14: limits CHG node current into the 3 V GPIO; R5: Q2 gate
R15 R12,2,10k,Resistor_SMD:R_0402_1005Metric,R15: booster FET gate pull-down; R12: BS0 low = 4-wire SPI
SW1,1,BUTTON,Button_Switch_SMD:SW_SPST_EVQP7A,Panasonic EVQ-P7A side-press
TH1,1,10k B3380,Resistor_SMD:R_0402_1005Metric,"Murata NCP15XH103F03RC, touching the cell"
TP1,1,3V0,TestPoint:TestPoint_Pad_1.0x1.0mm,SWD
TP2,1,SWDIO,TestPoint:TestPoint_Pad_1.0x1.0mm,SWD
TP3,1,SWDCLK,TestPoint:TestPoint_Pad_1.0x1.0mm,SWD
TP4,1,RESET,TestPoint:TestPoint_Pad_1.0x1.0mm,SWD
TP5,1,GND,TestPoint:TestPoint_Pad_1.0x1.0mm,SWD
U1,1,MDBT50Q-1MV2,RF_Module:Raytac_MDBT50Q,"Raytac nRF52840 module, chip antenna"
U2,1,BQ25101,OpenEPin:Texas_YFP0006_DSBGA-6_0.9x1.6mm_P0.4mm,"TI BQ25101YFPR (YFP0006, 0.4 mm pitch)"
U3,1,TPS7A0230,Package_TO_SOT_SMD:SOT-23-5,TI TPS7A0230PDBVR
U4,1,TPS22916C,OpenEPin:Texas_YFP0004_DSBGA-4_0.78x0.78mm_P0.4mm,"TI TPS22916CYFPR (YFP0004, 0.4 mm pitch)"
U5,1,USBLC6-2SC6,Package_TO_SOT_SMD:SOT-23-6,ST USBLC6-2SC6
BAT,1,"LiPo 3.7 V 60 mAh, JST-PH, with protection circuit",not on board,x2robotics 60 mAh pouch (16 x 13 x 4 mm); option: CM Batteries 55 mAh 2.5 mm custom cell
DISP,1,GDEH0169E02,not on board,Good Display 1.69in round 400x400 Spectra 6 e-paper
